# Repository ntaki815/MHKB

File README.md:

# MHKB
Keyboard data to create a mechanical keyboard based on HHKB JIS layout

## Overview

HHKBのJIS配列を元にした自作キーボードを作成するための設計データです。

## Design Steps

### 1. Creating a Keyboard Layout
1. オンラインのキーボードレイアウトサイト（[Keyboard-Layout-Editor.com](http://www.keyboard-layout-editor.com/)）を利用して、HHKBのキー配列に合わせてキーを配置していきます。

2. 配置が完了したら右上のDownloadボタンから、SVG・PNG・JSONファイルをダウンロードします。

### 2. Preparation of PCB
1. 基板設計のためのツール[KiCAD](https://www.kicad.org/)をインストールします。

2. 自動配線のためのツール[Freerouting](https://github.com/freerouting/freerouting)をgithubリポジトリからダウンロードしてインストールします。

3. [yskoht/keyboard-layouterのリポジトリ](https://github.com/yskoht/keyboard-layouter)からPCB設計時にKeyboard-Layout-Editorで作成したレイアウトに沿ってスイッチを自動配置してくれるKiCADのプラグインを取得しておきます。

4. keyboard-layouterで読み込めるようKeyboard-Layout-Editorで作成したレイアウトのキーレジェンドを番号に変えておきます。

5. キーボード作成に使用するパーツのフットプリント等を[foostan/kbdのリポジトリ](https://github.com/foostan/kbd)から取得しておきます。

### 3. Schematic Design
1. KiCADを起動し、新規プロジェクトを作成します。

2. .kicad_schファイルを選択して回路図エディターを開きます。

3. 設定＞シンボルライブラリーを管理 からシンボルライブラリーを開き、[foostan/kbdのリポジトリ](https://github.com/foostan/kbd)から取得したシンボルを追加します。

4. ProMicro、スイッチやダイオードを配置して回路図を書いていきます。（詳細は割愛）
    + ProMicroで使用できるピン数が限られており、本キーボードは69キーあるため、7行×10列で格子状に回路を組みます。
    + 検査＞エレクトリカル ルール チェッカー(ERC) からERCを実行して問題ないことを確認します。

5. ツール＞フットプリントを割り当て から配置したシンボルに対してフットプリントを割り当てていきます。

6. ツール＞回路図から基板を更新 にて作成した回路図の内容を基板に反映します。
    + KiCAD 6.0~からネットリストがなくなり直接PCBエディターのほうに反映できるようになったようです。

### 4. PCB Design
1. .kicad_pcbファイルを選択してPCBエディターを開きます。

2. ツール＞外部プラグイン＞プラグイン ディレクトリーを開く からディレクトリーを開き、keyboard_layouter.pyのファイルを配置します。

3. ツール＞外部プラグイン＞プラグインを更新 を押下してプラグインを読み込みます。

4. ツール＞外部プラグイン＞Keyboard Layouter を押下してプラグインを起動します。

5. Keyboard-Layout-Editorで作成した（Preparation of PCBのフェーズで番号を振った方の）JSONファイルを指定してRunを実行します。

6. ProMicroやReset SW等のパーツを配置してレイアウトを整えます。

7. ファイル＞エクスポート＞Specctra DSN... から.dsnファイルをエクスポートします。

8. Freeroutingを起動し、Open Your Own Designからエクスポートした.dsnファイルを選択します。

9. Autorouterを押下して自動配線を実行します。

10. Completeになったら、File＞Export Specctra Session File を押下して.sesファイルに出力します。

11. KiCADのPCBエディターに戻り、ファイル＞インポート＞Specctra セッション... から.sesファイルをインポートします。

12. 検査＞デザインルール チェッカー からデザインルール チェッカーを実行し、エラー箇所を特定します。

13. Holeに配線が近すぎる等のエラーが大半だと思うので、エラーがなくなるまでマニュアルで修正をしていきます。

14. Edge.cutsのレイヤーを選択し、外線を引いていきます。

15. 塗りつぶしゾーンを追加を選択し、F.Cu・B.CuのGNDに対して塗りつぶしをします。

16. ファイル＞プロット... から製造ファイルを出力します。

### 5. Plate Design
1. オンラインのキーボードレイアウトサイト（[Plate & Case Builder](http://builder.swillkb.com/)）を利用して、SWをはめ込むためのトッププレートを設計します。

2. サイトを開いたらKeyboard-Layout-Editorで作成したレイアウトのRaw dataをコピーして、Plate Layoutに貼り付けます。

3. Switch TypeにMX{_t:3}を選択

4. Case TypeにPoker - 60%を選択

5. Plate CornersをONにしてradiusに2mmを指定

6. Draw My CAD!!! を押下

7. CAD Outputのタブを開き、svg・dxfファイルをダウンロードします。

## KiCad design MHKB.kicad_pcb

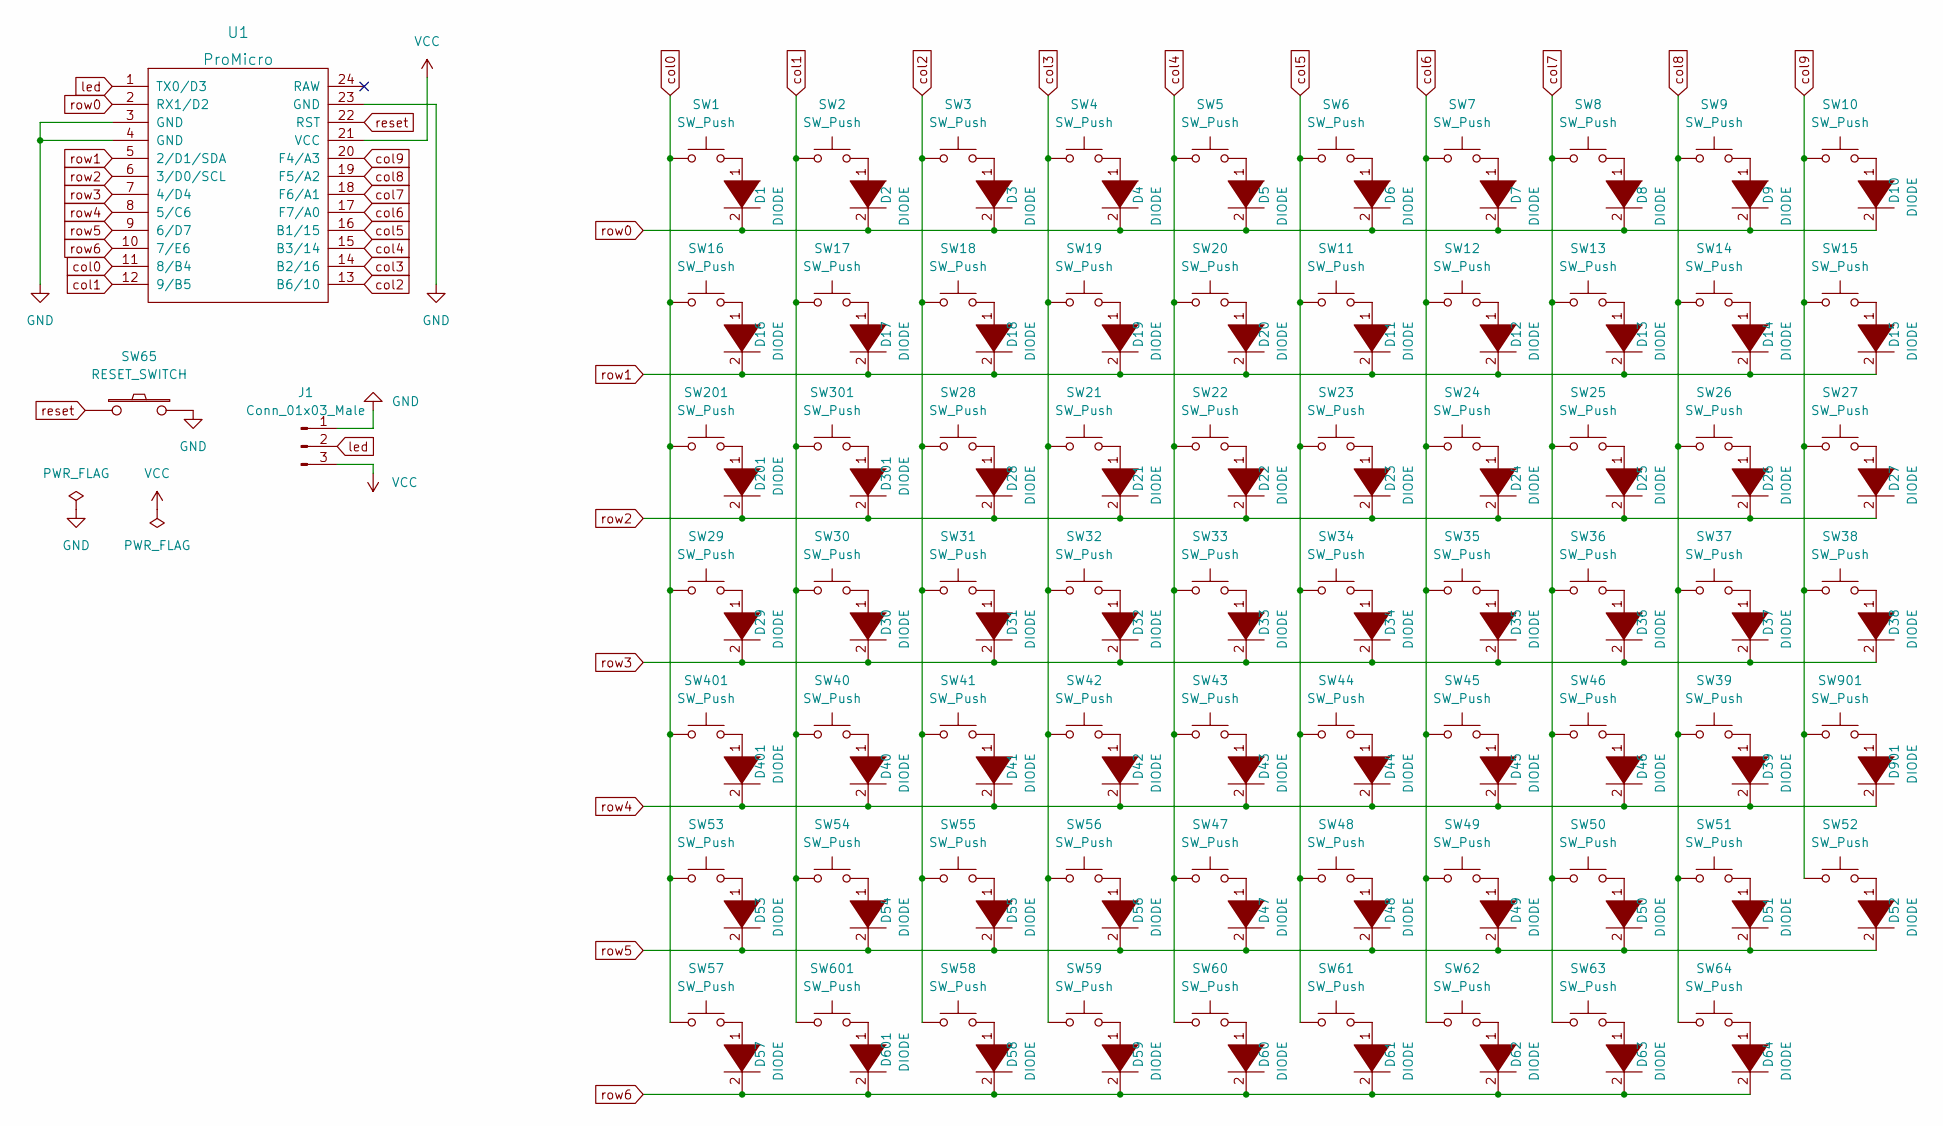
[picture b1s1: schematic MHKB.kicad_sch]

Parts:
D1, D2, D3, D4, D5, D6, D7, D8, D9, D10, D11, D12, D13, D14, D15, D16, D17, D18, D19, D20, D21, D22, D23, D24, D25, D26, D27, D28, D29, D30, D31, D32, D33, D34, D35, D36, D37, D38, D39, D40, D41, D42, D43, D44, D45, D46, D47, D48, D49, D50, D51, D52, D53, D54, D55, D56, D57, D58, D59, D60, D61, D62, D63, D64, D201, D301, D401, D601, D901: DIODE; D3_TH_SMD_v2
J1: Conn_01x03_Male; StripLED_rev
SW1, SW2, SW3, SW4, SW5, SW6, SW7, SW8, SW9, SW10, SW11, SW12, SW13, SW14, SW15, SW16, SW17, SW18, SW19, SW20, SW21, SW22, SW23, SW24, SW25, SW26, SW27, SW28, SW29, SW30, SW31, SW32, SW33, SW34, SW35, SW36, SW37, SW38, SW39, SW40, SW41, SW42, SW43, SW44, SW45, SW46, SW47, SW48, SW49, SW50, SW51, SW52, SW53, SW54, SW55, SW56, SW57, SW58, SW59, SW60, SW61, SW62, SW63, SW64, SW201, SW301, SW401, SW601, SW901: SW_Push; CherryMX_Hotswap
SW65: RESET_SWITCH; ResetSW
U1: ProMicro; ProMicro_v2

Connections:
GND: J1.1, SW65.2, U1.3 (GND), U1.4 (GND), U1.23 (GND)
unnamed: D1.1 (K), SW1.2
unnamed: D2.1 (K), SW2.2
unnamed: D3.1 (K), SW3.2
unnamed: D4.1 (K), SW4.2
unnamed: D5.1 (K), SW5.2
unnamed: D6.1 (K), SW6.2
unnamed: D7.1 (K), SW7.2
unnamed: D8.1 (K), SW8.2
unnamed: D9.1 (K), SW9.2
unnamed: D10.1 (K), SW10.2
unnamed: D11.1 (K), SW11.2
unnamed: D12.1 (K), SW12.2
unnamed: D13.1 (K), SW13.2
unnamed: D14.1 (K), SW14.2
unnamed: D15.1 (K), SW15.2
unnamed: D16.1 (K), SW16.2
unnamed: D17.1 (K), SW17.2
unnamed: D18.1 (K), SW18.2
unnamed: D19.1 (K), SW19.2
unnamed: D20.1 (K), SW20.2
unnamed: D21.1 (K), SW21.2
unnamed: D22.1 (K), SW22.2
unnamed: D23.1 (K), SW23.2
unnamed: D24.1 (K), SW24.2
unnamed: D25.1 (K), SW25.2
unnamed: D26.1 (K), SW26.2
unnamed: D27.1 (K), SW27.2
unnamed: D28.1 (K), SW28.2
unnamed: D29.1 (K), SW29.2
unnamed: D30.1 (K), SW30.2
unnamed: D31.1 (K), SW31.2
unnamed: D32.1 (K), SW32.2
unnamed: D33.1 (K), SW33.2
unnamed: D34.1 (K), SW34.2
unnamed: D35.1 (K), SW35.2
unnamed: D36.1 (K), SW36.2
unnamed: D37.1 (K), SW37.2
unnamed: D38.1 (K), SW38.2
unnamed: D39.1 (K), SW39.2
unnamed: D40.1 (K), SW40.2
unnamed: D41.1 (K), SW41.2
unnamed: D42.1 (K), SW42.2
unnamed: D43.1 (K), SW43.2
unnamed: D44.1 (K), SW44.2
unnamed: D45.1 (K), SW45.2
unnamed: D46.1 (K), SW46.2
unnamed: D47.1 (K), SW47.2
unnamed: D48.1 (K), SW48.2
unnamed: D49.1 (K), SW49.2
unnamed: D50.1 (K), SW50.2
unnamed: D51.1 (K), SW51.2
unnamed: D52.1 (K), SW52.2
unnamed: D53.1 (K), SW53.2
unnamed: D54.1 (K), SW54.2
unnamed: D55.1 (K), SW55.2
unnamed: D56.1 (K), SW56.2
unnamed: D57.1 (K), SW57.2
unnamed: D58.1 (K), SW58.2
unnamed: D59.1 (K), SW59.2
unnamed: D60.1 (K), SW60.2
unnamed: D61.1 (K), SW61.2
unnamed: D62.1 (K), SW62.2
unnamed: D63.1 (K), SW63.2
unnamed: D64.1 (K), SW64.2
unnamed: D201.1 (K), SW201.2
unnamed: D301.1 (K), SW301.2
unnamed: D401.1 (K), SW401.2
unnamed: D601.1 (K), SW601.2
unnamed: D901.1 (K), SW901.2
VCC: J1.3, U1.21 (VCC)
col0: SW1.1, SW16.1, SW29.1, SW53.1, SW57.1, SW201.1, SW401.1, U1.11 (8/B4)
col1: SW2.1, SW17.1, SW30.1, SW40.1, SW54.1, SW301.1, SW601.1, U1.12 (9/B5)
col2: SW3.1, SW18.1, SW28.1, SW31.1, SW41.1, SW55.1, SW58.1, U1.13 (B6/10)
col3: SW4.1, SW19.1, SW21.1, SW32.1, SW42.1, SW56.1, SW59.1, U1.14 (B2/16)
col4: SW5.1, SW20.1, SW22.1, SW33.1, SW43.1, SW47.1, SW60.1, U1.15 (B3/14)
col5: SW6.1, SW11.1, SW23.1, SW34.1, SW44.1, SW48.1, SW61.1, U1.16 (B1/15)
col6: SW7.1, SW12.1, SW24.1, SW35.1, SW45.1, SW49.1, SW62.1, U1.17 (F7/A0)
col7: SW8.1, SW13.1, SW25.1, SW36.1, SW46.1, SW50.1, SW63.1, U1.18 (F6/A1)
col8: SW9.1, SW14.1, SW26.1, SW37.1, SW39.1, SW51.1, SW64.1, U1.19 (F5/A2)
col9: SW10.1, SW15.1, SW27.1, SW38.1, SW52.1, SW901.1, U1.20 (F4/A3)
led: J1.2, U1.1 (TX0/D3)
reset: SW65.1, U1.22 (RST)
row0: D1.2 (A), D2.2 (A), D3.2 (A), D4.2 (A), D5.2 (A), D6.2 (A), D7.2 (A), D8.2 (A), D9.2 (A), D10.2 (A), U1.2 (RX1/D2)
row1: D11.2 (A), D12.2 (A), D13.2 (A), D14.2 (A), D15.2 (A), D16.2 (A), D17.2 (A), D18.2 (A), D19.2 (A), D20.2 (A), U1.5 (2/D1/SDA)
row2: D21.2 (A), D22.2 (A), D23.2 (A), D24.2 (A), D25.2 (A), D26.2 (A), D27.2 (A), D28.2 (A), D201.2 (A), D301.2 (A), U1.6 (3/D0/SCL)
row3: D29.2 (A), D30.2 (A), D31.2 (A), D32.2 (A), D33.2 (A), D34.2 (A), D35.2 (A), D36.2 (A), D37.2 (A), D38.2 (A), U1.7 (4/D4)
row4: D39.2 (A), D40.2 (A), D41.2 (A), D42.2 (A), D43.2 (A), D44.2 (A), D45.2 (A), D46.2 (A), D401.2 (A), D901.2 (A), U1.8 (5/C6)
row5: D47.2 (A), D48.2 (A), D49.2 (A), D50.2 (A), D51.2 (A), D52.2 (A), D53.2 (A), D54.2 (A), D55.2 (A), D56.2 (A), U1.9 (6/D7)
row6: D57.2 (A), D58.2 (A), D59.2 (A), D60.2 (A), D61.2 (A), D62.2 (A), D63.2 (A), D64.2 (A), D601.2 (A), U1.10 (7/E6)

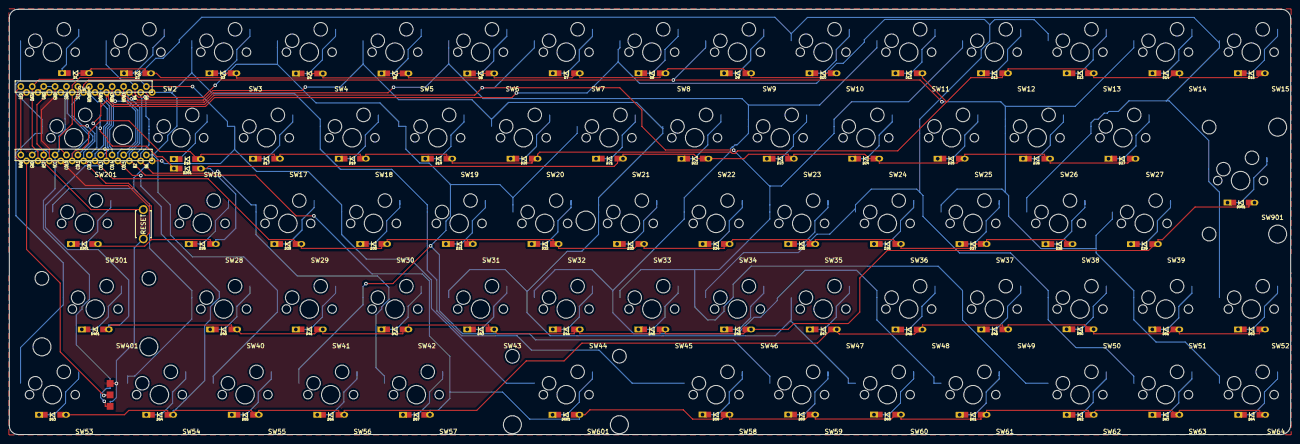
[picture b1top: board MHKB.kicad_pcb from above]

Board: 2 copper layers, 285.0 x 94.6 mm, 158 parts (0 on the bottom side), 90 nets.

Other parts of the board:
Ref1: Val1; M2_HOLE_v2
Ref2: Ref2
Ref3: Ref3
Ref4: Ref4
Ref5: Ref5
Ref6: Ref6
Ref7: Ref7
Ref8: Ref8
Ref9: Ref9
Ref10: Ref10
Ref11: Ref11
Ref12: Ref12
Ref13: Ref13
Ref14: Ref14
Ref15: Ref15
Ref16: Ref16
Ref17: Ref17

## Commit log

2022-06-11 設計ファイル追加
2022-06-11 legendを修正し、画像ファイルを追加
2022-06-11 作成手順を追記
